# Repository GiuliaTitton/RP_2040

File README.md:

# Descrizione del File main.c

**Nome del File**: main.c
**Progetto**: PSE_2021_2022_SERVER_NTP_LAN
**Cartella**: /FW/TEST_RTC_GPS

## Descrizione
Il programma `main.c` acquisisce l'orario da un modulo GPS e dal RTC (Real-Time Clock) e ne confronta i valori. Se i valori sono diversi, reimposta l'orario del RTC con i valori acquisiti dal GPS. Il programma è diviso in varie sezioni:

1. **Setup dei LED GPIO**: Viene configurato il GPIO per fornire un feedback visivo tramite LED.
2. **Setup di interrupt e interfaccia UART GPS**: Vengono configurati gli interrupt e l'interfaccia UART per comunicare con il modulo GPS.
3. **Lampeggio dei LED**: Viene implementato un lampeggio dei LED per scopi di debug.
4. **Setup I2C e orario iniziale RTC**: Si inizializza la comunicazione I2C e si imposta l'orario iniziale del RTC.
5. **Impostazione dell'allarme**: L'allarme non è impostato nella versione attuale.
6. **Loop continuo composto da**:
   - Lampeggio dei LED.
   - Acquisizione dei dati dal modulo GPS.
   - Acquisizione dei dati dal RTC.
   - Confronto dei dati acquisiti dal modulo GPS e dal RTC.
7. **Controllo dei messaggi in ricezione dal modulo GPS**: Viene gestita la ricezione dei messaggi dal modulo GPS.

## Note
L'allarme non è attualmente impostato nel programma, ma può essere utilizzato per il confronto dei dati acquisiti.

## Autori
- PAGANIN ANDREA
- PASQUINI GIUSEPPE
- TRENTI ELIA
- TITTON GIULIA
- AMORTH MATTEO

## Cambiamenti
- F26/05, Versione A.00.01, 26 Maggio 2022, M. A.: Aggiunte descrizioni delle funzioni e intestazione.
- F19/06, Versione A.00.02, 19 Giugno 2023, M. A.: Aggiunto reset LAN per problema di connessione.

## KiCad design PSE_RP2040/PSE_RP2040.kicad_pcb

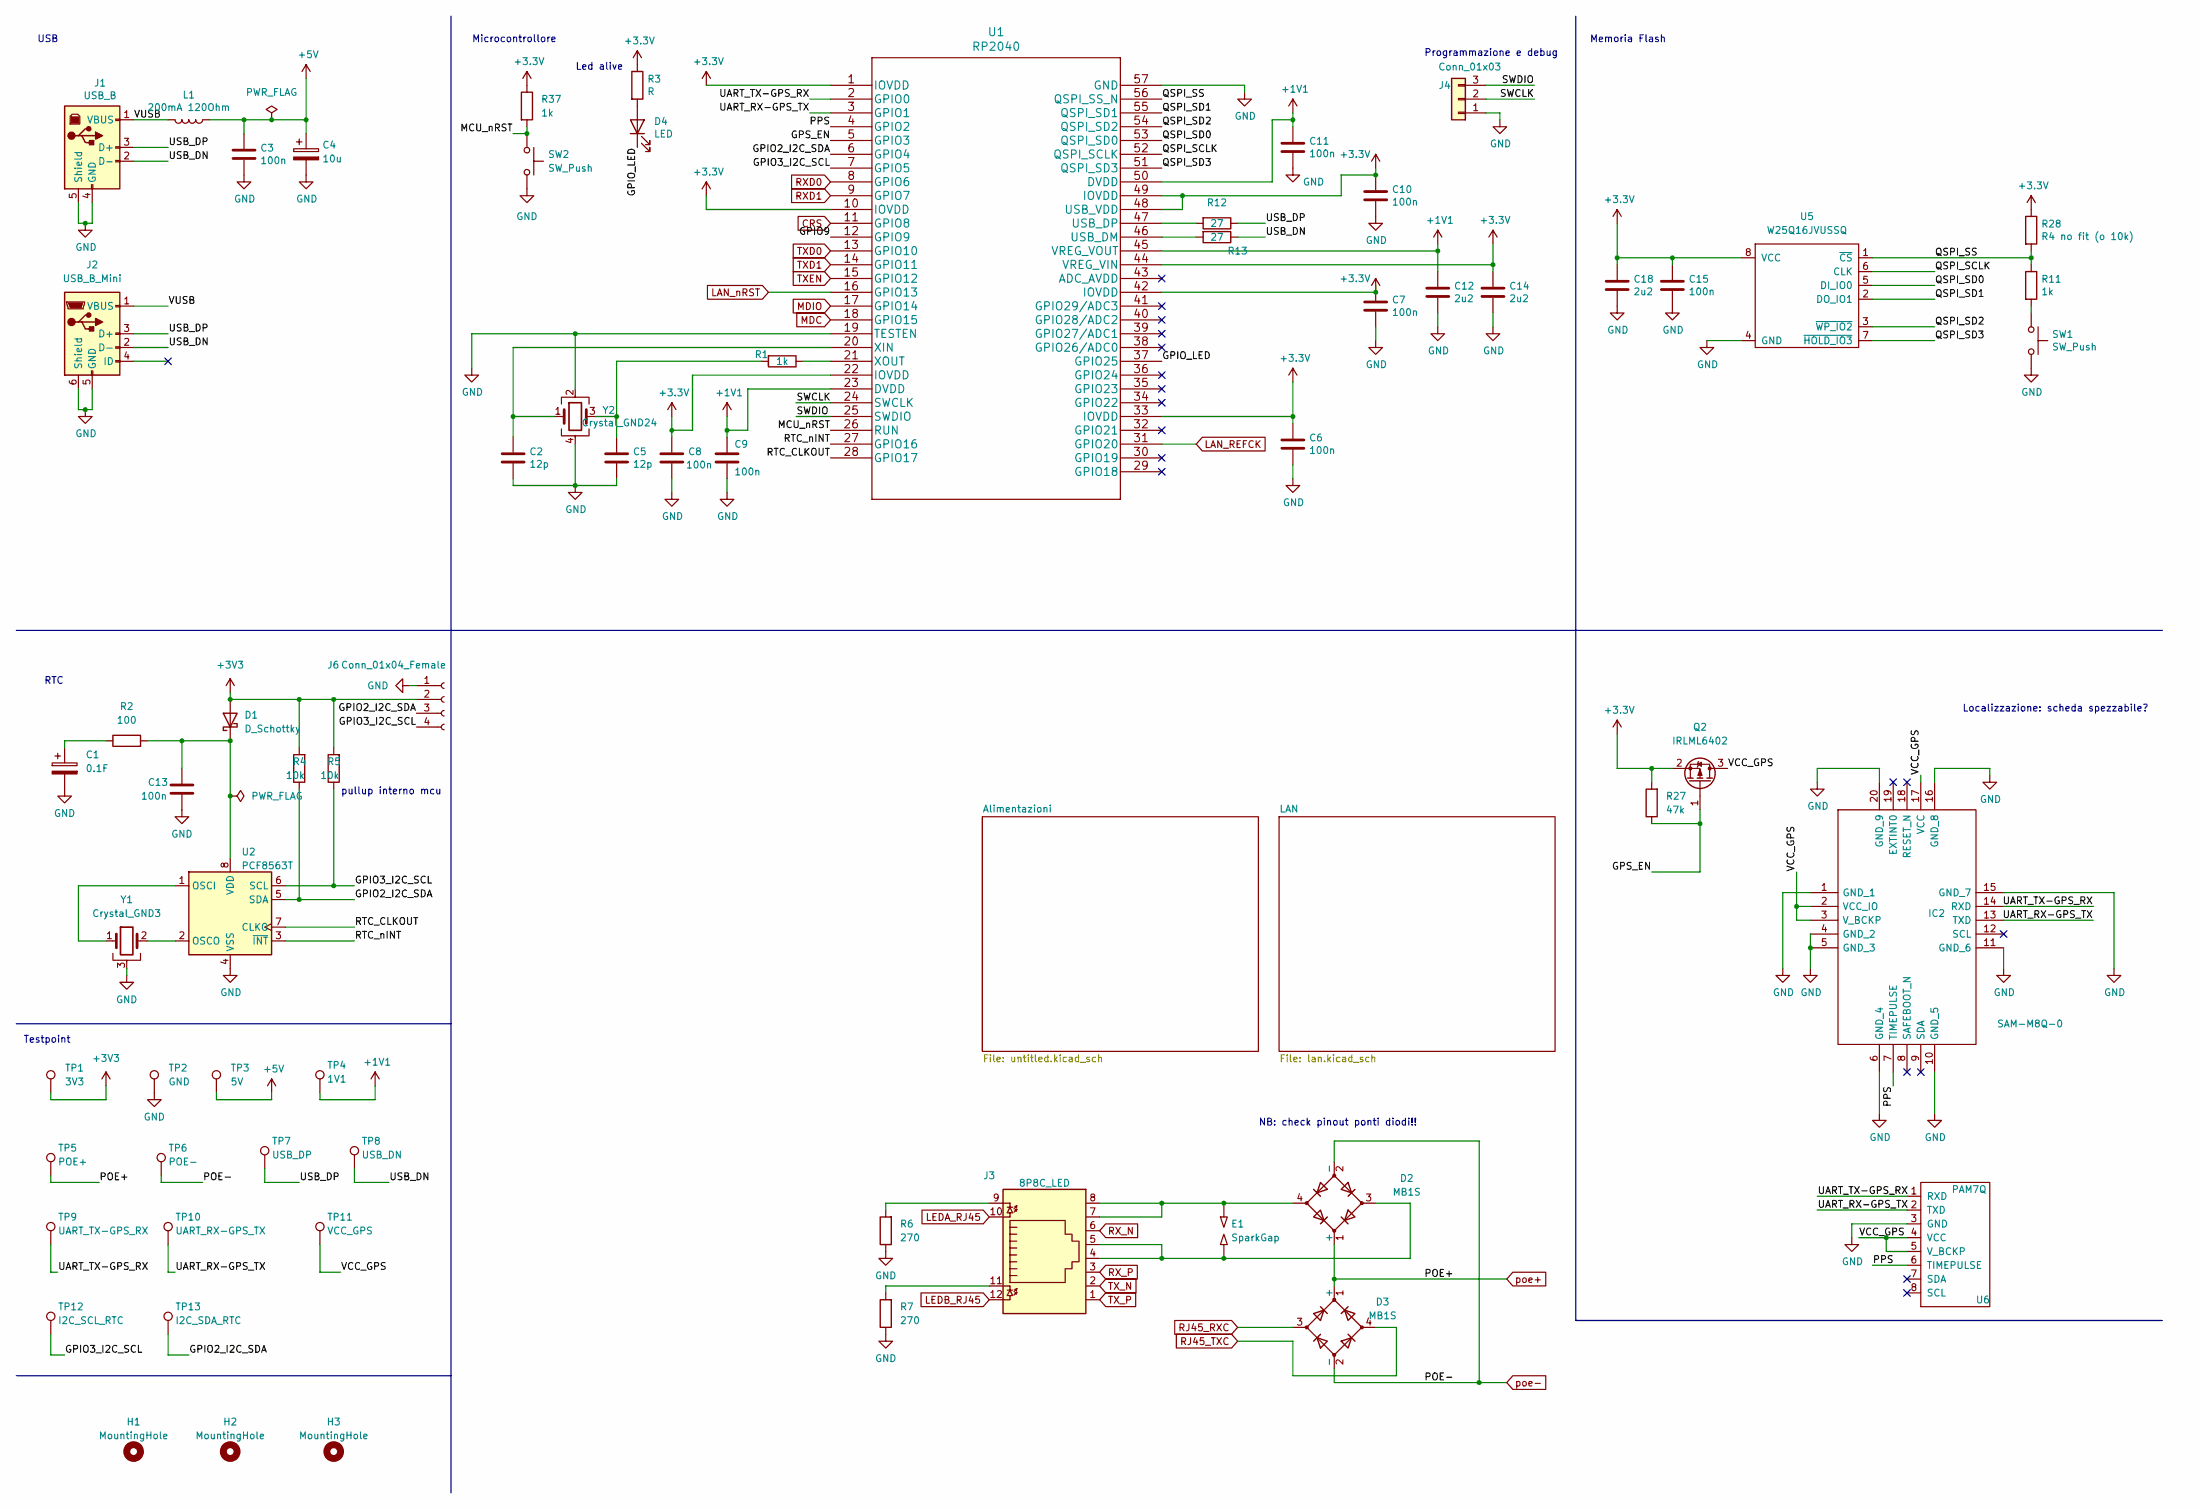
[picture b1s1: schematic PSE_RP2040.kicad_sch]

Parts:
C1: 0.1F; CP_Radial_D10.0mm_P5.00mm
C2, C5: 12p; C_0603_1608Metric
C3, C6, C7, C8, C9, C10, C11, C13, C15: 100n; C_0603_1608Metric
C4: 10u; C_0805_2012Metric
C12, C14, C18: 2u2; C_0603_1608Metric
D1: D_Schottky; D_SMA
D2, D3: MB1S; SO-4_4.4x3.6mm_P2.54mm
D4: LED; LED_0603_1608Metric
E1: SparkGap; SPARK_GAP_TRIANGLE
H1, H2, H3: MountingHole; MountingHole_3mm
IC2: SAM-M8Q-0; SAM-M8Q; Manufacturer_Part_Number SAM-M8Q-0; Mouser Part Number 377-SAM-M8Q-0
J1: USB_B; USB_B_OST_USB-B1HSxx_Horizontal
J2: USB_B_Mini; USB_Mini-B_Wuerth_65100516121_Horizontal
J3: 8P8C_LED; RJ45_Amphenol_RJHSE-5081
J4: Conn_01x03; PinHeader_1x03_P2.54mm_Vertical
J6: Conn_01x04_Female; PinHeader_1x04_P2.54mm_Vertical
L1: 200mA 120Ohm; L_0603_1608Metric
Q2: IRLML6402; SOT-23
R1, R11, R37: 1k; R_0603_1608Metric
R2: 100; R_0603_1608Metric
R3: R; R_0603_1608Metric
R4, R5: 10k; R_0603_1608Metric
R6, R7: 270; R_0603_1608Metric
R12, R13: 27; R_0603_1608Metric
R27: 47k; R_0603_1608Metric
R28: R4 no fit (o 10k); R_0603_1608Metric
SW1, SW2: SW_Push; SW_PUSH_6mm
TP1: 3V3; TestPoint_Loop_D1.80mm_Drill1.0mm_Beaded
TP2: GND; TestPoint_Loop_D1.80mm_Drill1.0mm_Beaded
TP3: 5V; TestPoint_Pad_D1.0mm
TP4: 1V1; TestPoint_Pad_D1.0mm
TP5: POE+; TestPoint_Pad_D1.0mm
TP6: POE-; TestPoint_Pad_D1.0mm
TP7: USB_DP; TestPoint_Pad_D1.0mm
TP8: USB_DN; TestPoint_Pad_D1.0mm
TP9: UART_TX-GPS_RX; TestPoint_Pad_D1.0mm
TP10: UART_RX-GPS_TX; TestPoint_Pad_D1.0mm
TP11: VCC_GPS; TestPoint_Pad_D1.0mm
TP12: I2C_SCL_RTC; TestPoint_Pad_D1.0mm
TP13: I2C_SDA_RTC; TestPoint_Pad_D1.0mm
U1: RP2040; RP2040-QFN-56
U2: PCF8563T; SOIC-8_3.9x4.9mm_P1.27mm
U5: W25Q16JVUSSQ; SOIC-8_5.275x5.275mm_P1.27mm
U6: PAM7Q; PAM-7Q
Y1: Crystal_GND3; Crystal_AT310_D3.0mm_L10.0mm_Horizontal_1EP_style1
Y2: Crystal_GND24; Crystal_SMD_3225-4Pin_3.2x2.5mm

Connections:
+1V1: C9.1, C11.1, C12.1, TP4.1, U1.23 (DVDD), U1.45 (VREG_VOUT), U1.50 (DVDD)
+5V: C3.1, C4.1, L1.1, TP3.1; also elsewhere on the board
/GPIO2_I2C_SDA: J6.3, R4.1, TP13.1, U1.6 (GPIO4), U2.5 (SDA)
/GPIO3_I2C_SCL: J6.4, R5.1, TP12.1, U1.7 (GPIO5), U2.6 (SCL)
/GPIO9: U1.12 (GPIO9)
/GPIO_LED: D4.1 (K), U1.37 (GPIO25)
/GPS_EN: Q2.1 (G), R27.1, U1.5 (GPIO3)
/MCU_nRST: R37.2, SW2.1, U1.26 (RUN)
/PPS: IC2.7 (TIMEPULSE), U1.4 (GPIO2), U6.6 (TIMEPULSE)
/QSPI_SCLK: U1.52 (QSPI_SCLK), U5.6 (CLK)
/QSPI_SD0: U1.53 (QSPI_SD0), U5.5 (DI_IO0)
/QSPI_SD1: U1.55 (QSPI_SD1), U5.2 (DO_IO1)
/QSPI_SD2: U1.54 (QSPI_SD2), U5.3 (~WP_IO2)
/QSPI_SD3: U1.51 (QSPI_SD3), U5.7 (~HOLD_IO3)
/QSPI_SS: R11.1, R28.2, U1.56 (QSPI_SS_N), U5.1 (~CS)
/RTC_CLKOUT: U1.28 (GPIO17), U2.7 (CLKO)
/RTC_nINT: U1.27 (GPIO16), U2.3 (~INT)
/SWCLK: J4.2, U1.24 (SWCLK)
/SWDIO: J4.3, U1.25 (SWDIO)
/UART_RX-GPS_TX: IC2.13 (TXD), TP10.1, U1.3 (GPIO1), U6.2 (TXD)
/UART_TX-GPS_RX: IC2.14 (RXD), TP9.1, U1.2 (GPIO0), U6.1 (RXD)
/USB_DN: J1.2 (D-), J2.2 (D-), R13.1, TP8.1
/USB_DP: J1.3 (D+), J2.3 (D+), R12.1, TP7.1
/VCC_GPS: IC2.2 (VCC_IO), IC2.3 (V_BCKP), IC2.17 (VCC), Q2.3 (D), TP11.1, U6.4 (VCC), U6.5 (V_BCKP)
/VUSB: J1.1 (VBUS), J2.1 (VBUS), L1.2
CRS: U1.11 (GPIO8); also elsewhere on the board
GND: C1.2, C2.2, C3.2, C4.2, C5.2, C6.2, C7.2, C8.2, C9.2, C10.2, C11.2, C12.2, C13.2, C14.2, C15.2, C18.2, IC2.1 (GND_1), IC2.4 (GND_2), IC2.5 (GND_3), IC2.6 (GND_4), IC2.10 (GND_5), IC2.11 (GND_6), IC2.15 (GND_7), IC2.16 (GND_8), IC2.20 (GND_9), J1.4 (GND), J1.5 (Shield), J2.5 (GND), J2.6 (Shield), J4.1, J6.1, R6.1, R7.1, SW1.2, SW2.2, TP2.1, U1.19 (TESTEN), U1.57 (GND), U2.4 (VSS), U5.4 (GND), U6.3 (GND), Y1.3, Y2.2, Y2.4; also elsewhere on the board
LAN_REFCK: U1.31 (GPIO20); also elsewhere on the board
LAN_nRST: U1.16 (GPIO13); also elsewhere on the board
LEDA_RJ45: J3.10; also elsewhere on the board
LEDB_RJ45: J3.12; also elsewhere on the board
MDC: U1.18 (GPIO15); also elsewhere on the board
MDIO: U1.17 (GPIO14); also elsewhere on the board
unnamed: C1.1, R2.1
unnamed: C2.1, U1.20 (XIN), Y2.1
unnamed: C5.1, R1.2, Y2.3
unnamed: D2.3, E1.1, J3.4, J3.5
unnamed: D2.4, E1.2, J3.7, J3.8
unnamed: D4.2 (A), R3.2
unnamed: J3.9, R6.2
unnamed: J3.11, R7.2
unnamed: R1.1, U1.21 (XOUT)
unnamed: R11.2, SW1.1
unnamed: R12.2, U1.47 (USB_DP)
unnamed: R13.2, U1.46 (USB_DM)
unnamed: U2.1 (OSCI), Y1.1
unnamed: U2.2 (OSCO), Y1.2
RJ45_RXC: D3.3; also elsewhere on the board
RJ45_TXC: D3.4; also elsewhere on the board
RXD0: U1.8 (GPIO6); also elsewhere on the board
RXD1: U1.9 (GPIO7); also elsewhere on the board
RX_N: J3.6; also elsewhere on the board
RX_P: J3.3; also elsewhere on the board
TXD0: U1.13 (GPIO10); also elsewhere on the board
TXD1: U1.14 (GPIO11); also elsewhere on the board
TXEN: U1.15 (GPIO12); also elsewhere on the board
TX_N: J3.2; also elsewhere on the board
TX_P: J3.1; also elsewhere on the board
poe+: D2.1 (+), D3.1 (+), TP5.1; also elsewhere on the board
poe-: D2.2 (-), D3.2 (-), TP6.1; also elsewhere on the board

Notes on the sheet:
Memoria Flash
USB
pullup interno mcu
RTC
Led alive
Programmazione e debug
Testpoint
NB: check pinout ponti diodi!!
Localizzazione: scheda spezzabile?
Microcontrollore

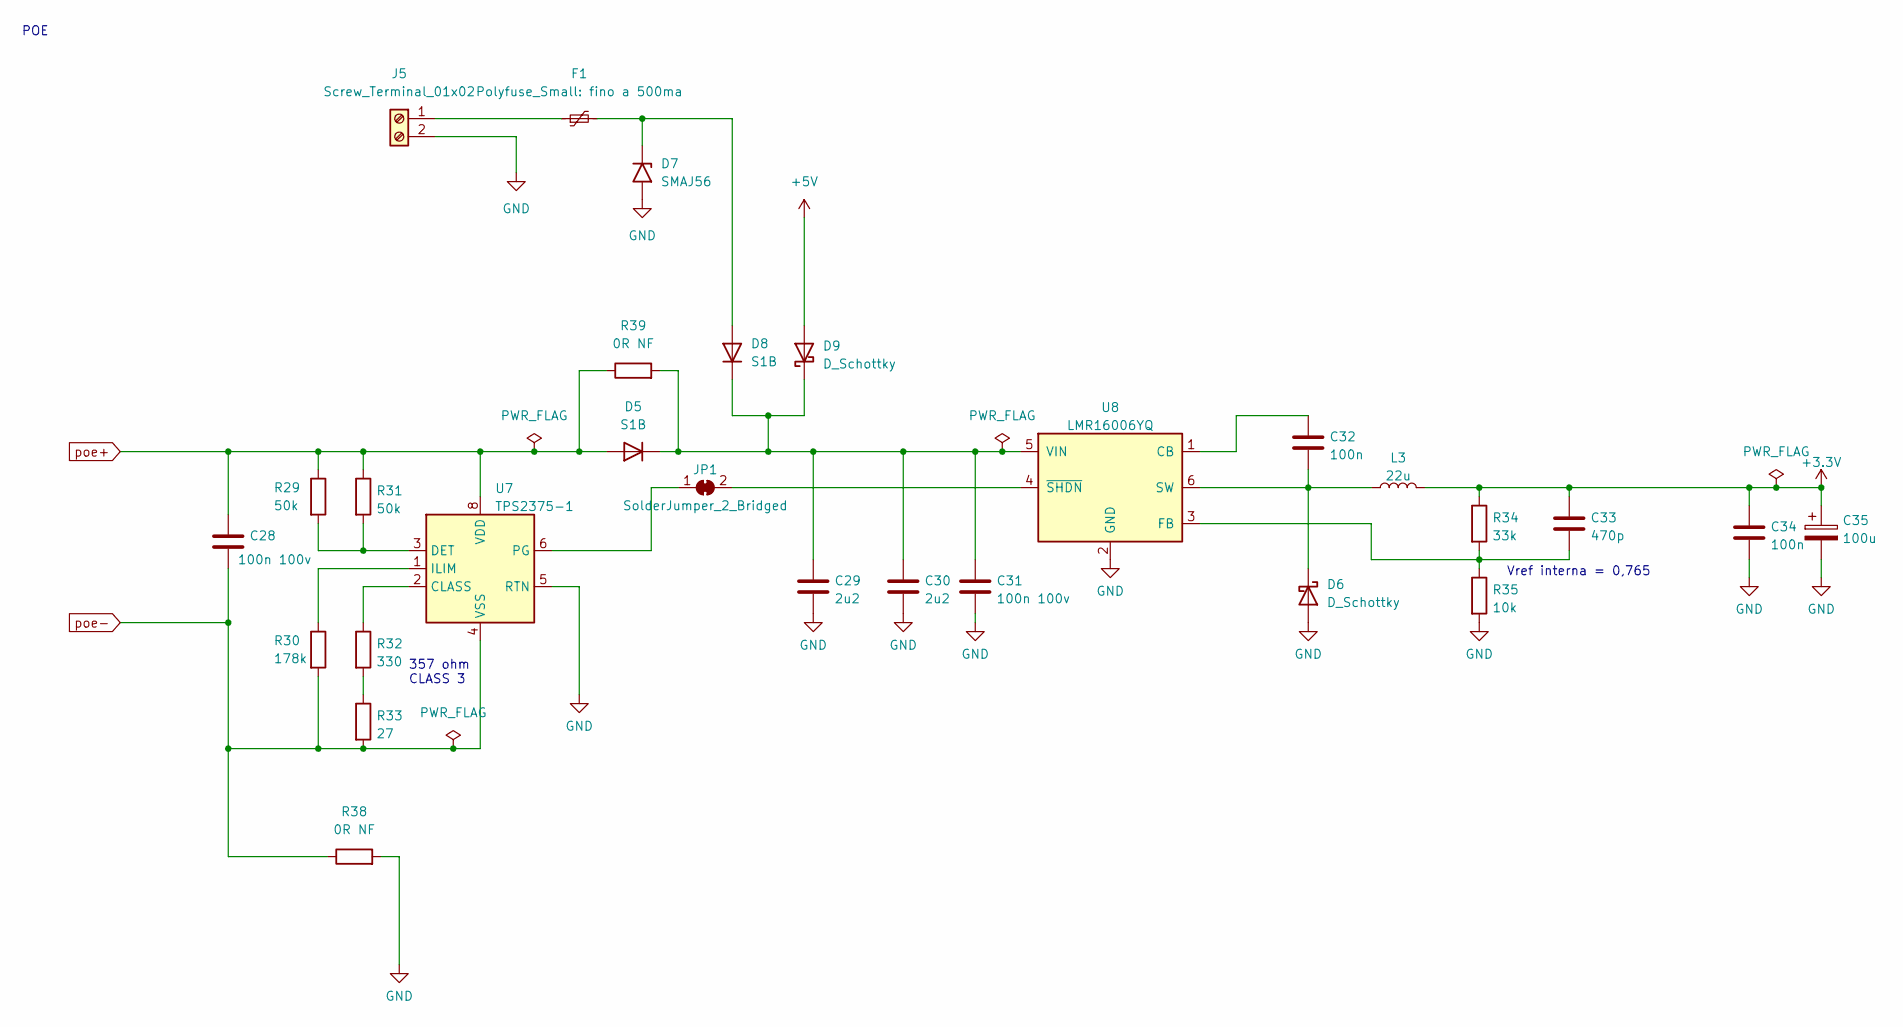
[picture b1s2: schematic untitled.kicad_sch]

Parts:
C28, C31: 100n 100v; C_0603_1608Metric
C29, C30: 2u2; C_0603_1608Metric
C32, C34: 100n; C_0603_1608Metric
C33: 470p; C_0603_1608Metric
C35: 100u; C_0805_2012Metric
D5, D8: S1B; D_SMA
D6, D9: D_Schottky; D_SMA
D7: SMAJ56; D_SMA
F1: Polyfuse_Small: fino a 500ma; Fuse_1812_4532Metric
J5: Screw_Terminal_01x02; TerminalBlock_Phoenix_MKDS-1,5-2-5.08_1x02_P5.08mm_Horizont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
JP1: SolderJumper_2_Bridged; SolderJumper-2_P1.3mm_Bridged_Pad1.0x1.5mm
L3: 22u; L_Vishay_IFSC-1515AH_4x4x1.8mm
R29, R31: 50k; R_0603_1608Metric
R30: 178k; R_0603_1608Metric
R32: 330; R_0603_1608Metric
R33: 27; R_0603_1608Metric
R34: 33k; R_0603_1608Metric
R35: 10k; R_0603_1608Metric
R38, R39: 0R NF; R_0603_1608Metric
U7: TPS2375-1; SOIC-8_5.275x5.275mm_P1.27mm
U8: LMR16006YQ; SOT-23-6

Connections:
+5V: D9.2 (A); also elsewhere on the board
GND: C29.2, C30.2, C31.2, C34.2, C35.2, D6.2 (A), D7.2 (A2), J5.2, R35.2, R38.2, U7.5 (RTN), U8.2 (GND); also elsewhere on the board
unnamed: C29.1, C30.1, C31.1, D5.1 (K), D8.1 (K), D9.1 (K), R39.2, U8.5 (VIN)
unnamed: C32.1, U8.1 (CB)
unnamed: C32.2, D6.1 (K), L3.1, U8.6 (SW)
unnamed: C33.2, R34.2, R35.1, U8.3 (FB)
unnamed: D7.1 (A1), D8.2 (A), F1.2
unnamed: F1.1, J5.1
unnamed: JP1.1 (A), U7.6 (PG)
unnamed: JP1.2 (B), U8.4 (~SHDN)
unnamed: R29.2, R31.2, U7.3 (DET)
unnamed: R30.1, U7.1 (ILIM)
unnamed: R32.1, U7.2 (CLASS)
unnamed: R32.2, R33.1
poe+: C28.1, D5.2 (A), R29.1, R31.1, R39.1, U7.8 (VDD); also elsewhere on the board
poe-: C28.2, R30.2, R33.2, R38.1, U7.4 (VSS); also elsewhere on the board

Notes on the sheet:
Vref interna = 0,765
POE
357 ohm CLASS 3

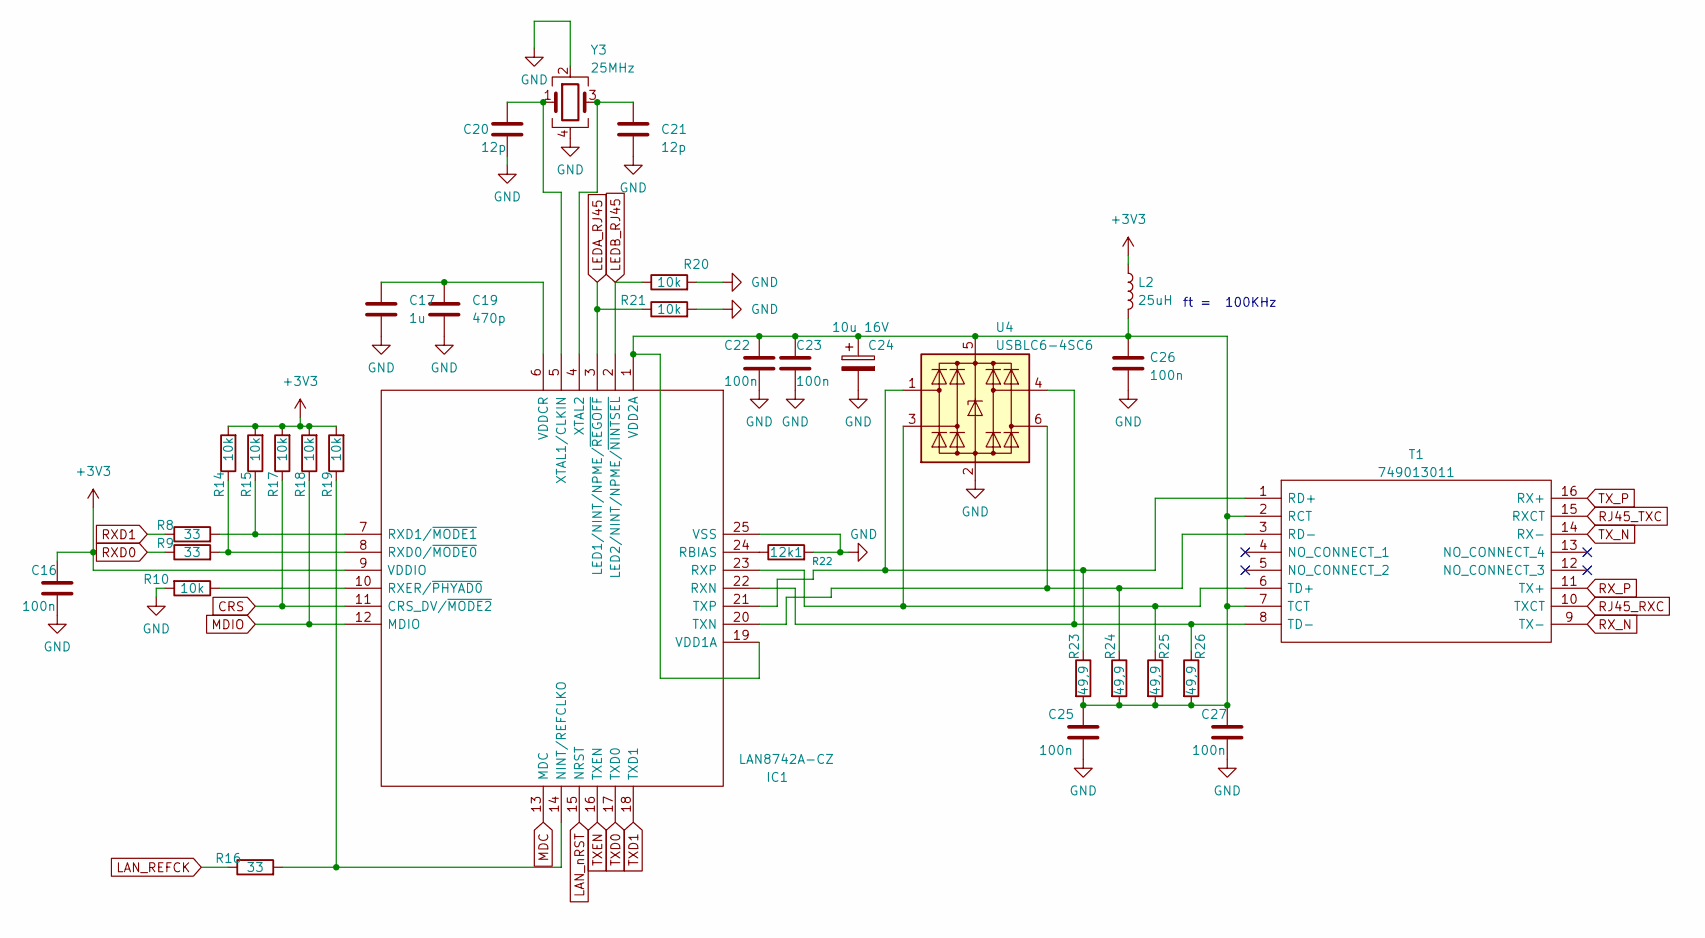
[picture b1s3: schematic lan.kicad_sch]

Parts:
C16, C22, C23, C25, C26, C27: 100n; C_0603_1608Metric
C17: 1u; C_0603_1608Metric
C19: 470p; C_0603_1608Metric
C20, C21: 12p; C_0603_1608Metric
C24: 10u 16V; C_0805_2012Metric
IC1: LAN8742A-CZ; HVQFN-24-1EP_4x4mm_P0.5mm_EP2.5x2.5mm_ThermalVias; Mouser Part Number 579-LAN8742A-CZ
L2: 25uH; L_0603_1608Metric
R8, R9, R16: 33; R_0603_1608Metric
R10, R14, R15, R17, R18, R19, R20, R21: 10k; R_0603_1608Metric
R22: 12k1; R_0603_1608Metric
R23, R24, R25, R26: 49,9; R_0603_1608Metric
T1: 749013011; Transformer_Ethernet_Wuerth_749013011A; Mouser Part Number 710-749013011
U4: USBLC6-4SC6; SOT-23-6
Y3: 25MHz; Crystal_SMD_3225-4Pin_3.2x2.5mm

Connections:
CRS: IC1.11 (CRS_DV/~MODE2), R17.1; also elsewhere on the board
GND: C16.2, C17.2, C19.2, C20.2, C21.2, C22.2, C23.2, C24.2, C25.2, C26.2, C27.2, IC1.25 (VSS), R10.2, R20.2, R21.2, R22.2, U4.2 (GND), Y3.2, Y3.4; also elsewhere on the board
LAN_REFCK: R16.1; also elsewhere on the board
LAN_nRST: IC1.15 (NRST); also elsewhere on the board
LEDA_RJ45: IC1.3 (LED1/NINT/NPME/~REGOFF), R21.1; also elsewhere on the board
LEDB_RJ45: IC1.2 (LED2/NINT/NPME/~NINTSEL), R20.1; also elsewhere on the board
MDC: IC1.13 (MDC); also elsewhere on the board
MDIO: IC1.12 (MDIO), R18.1; also elsewhere on the board
unnamed: C17.1, C19.1, IC1.6 (VDDCR)
unnamed: C20.1, IC1.5 (XTAL1/CLKIN), Y3.1
unnamed: C21.1, IC1.4 (XTAL2), Y3.3
unnamed: C22.1, C23.1, C24.1, C25.1, C26.1, C27.1, IC1.1 (VDD2A), IC1.19 (VDD1A), L2.2, R23.2, R24.2, R25.2, R26.2, T1.2 (RCT), T1.7 (TCT), U4.5 (VBUS)
unnamed: IC1.7 (RXD1/~MODE1), R8.2, R15.1
unnamed: IC1.8 (RXD0/~MODE0), R9.2, R14.1
unnamed: IC1.10 (RXER/~PHYAD0), R10.1
unnamed: IC1.14 (NINT/REFCLKO), R16.2, R19.1
unnamed: IC1.20 (TXN), R24.1, T1.3 (RD-), U4.6 (I/O4)
unnamed: IC1.21 (TXP), R23.1, T1.1 (RD+), U4.1 (I/O1)
unnamed: IC1.22 (RXN), R26.1, T1.8 (TD-), U4.4 (I/O3)
unnamed: IC1.23 (RXP), R25.1, T1.6 (TD+), U4.3 (I/O2)
unnamed: IC1.24 (RBIAS), R22.1
RJ45_RXC: T1.10 (TXCT); also elsewhere on the board
RJ45_TXC: T1.15 (RXCT); also elsewhere on the board
RXD0: R9.1; also elsewhere on the board
RXD1: R8.1; also elsewhere on the board
RX_N: T1.9 (TX-); also elsewhere on the board
RX_P: T1.11 (TX+); also elsewhere on the board
TXD0: IC1.17 (TXD0); also elsewhere on the board
TXD1: IC1.18 (TXD1); also elsewhere on the board
TXEN: IC1.16 (TXEN); also elsewhere on the board
TX_N: T1.14 (RX-); also elsewhere on the board
TX_P: T1.16 (RX+); also elsewhere on the board

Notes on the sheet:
ft = 100KHz

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
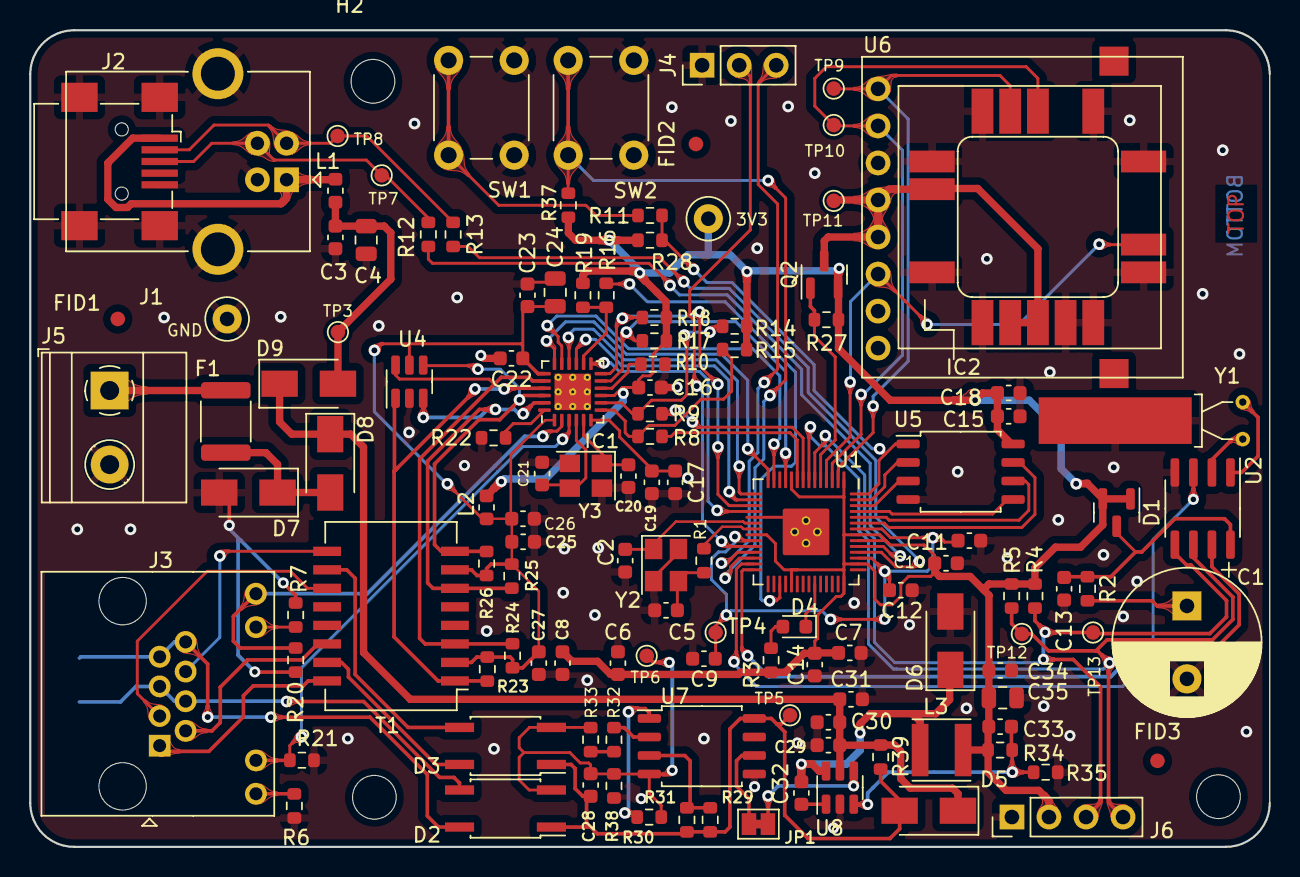
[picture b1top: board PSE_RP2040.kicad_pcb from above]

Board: 2 copper layers, 85.0 x 56.0 mm, 129 parts (1 on the bottom side), 86 nets.

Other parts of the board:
FID1, FID2, FID3: Fiducial_1mm_Mask2mm

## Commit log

2022-03-13 Aggiunta USB
2022-03-13 Create README.md
    commit di prova
2022-03-13 extracted files
2022-03-13 changed dir
2022-03-13 written prova4
2022-03-13 Revert "written prova4"
    This reverts commit d653c9951a9aa16452c87e5e3175ff5a990ef213.
2022-03-14 scritto prova matteo
2022-03-14 Update README.md
    bla bla
2022-03-15 Modifica schema kicad
    Aggiunti librerie, datasheet e componenti
2022-03-17 Modifica quarzo
2022-03-19 Aggiornamento schematico
    Passaggio a Kicad6, aggiunti elementi interfaccia LAN (iniziato)
2022-03-19 sostituzione componenti
2022-03-19 pt.2
2022-03-20 ds lan
2022-03-20 finito circuito lan
2022-03-20 USBLC6-4SC6 ds
2022-03-20 aggiunto pdf schematico(provvisorio)
2022-03-21 added fw folder
2022-03-21 added STRUTTURA_BASE to FW
2022-03-21 added bin
2022-03-21 trattino
2022-03-21 added pico-sdk
2022-03-21 test sdk
    Funziona. Aggiunto commento in cmake
2022-03-21 schematico completato
2022-03-21 PCF8563 Real time clock scheda dati
2022-03-21 rtc aggiunta
2022-03-21 Presentazione
2022-03-21 aggiunto datasheet pmos
2022-03-22 modifiche schematico
    cancellata sezione alimentazione non più necessaria (usiamo switching del poe)
2022-03-23 schematico
2022-03-23 backup file
2022-03-23 datasheet
2022-03-24 schematico rtc
2022-03-24 documentazione diodo
2022-03-24 aggiornamento schematico
2022-03-24 modifica cmakelists
    aggiunte impostazioni per il pull del pico-sdk
2022-03-24 annotato schematico + pwr flag
2022-03-25 aggiornato cmakelists.txt del fw
2022-03-26 modifica pull sdk
    tolto direttiva con percorso assoluto dell'sdk. avere sempre la cartella sdk parallela a quella di progetto.
2022-03-26 MountingHole+estetica
2022-03-28 footprint sam
2022-03-28 aggiunta libreria rp2040
2022-03-28 schematico
    Cambio trasformatore
    aggiunto foglio
2022-03-28 memoria
2022-03-28 Creata impronta base pam 7q (GPS2))
2022-03-29 aggiornamento schematico
    etichette globali, testpoint, assegnamento footprint (ne mancano ancora)
2022-03-29 assegnamento footprint PAM7Q
2022-03-29 footprint flash
2022-03-29 area pcb
2022-03-30 aggiunto Footprint sam-m8q e aggiornato pam-7q
    è una bozza, una volta controllate le misure si possono togliere le linee che ho messo per avere i riferimenti
2022-03-30 footprint usb micro e crystal
2022-03-30 footprint, aggiunto bottone rst
2022-03-30 OR a diodi, connettore ext PoE
2022-03-31 aggiunto pico-rmii-eth in FW
2022-03-31 tolta cartella build da FW/rmii
2022-03-31 valore resistenze lan
2022-03-31 correzioni schema
2022-03-31 update footprint
2022-04-01 Link super condensatore e connettore RJ45
2022-04-04 footprint, assegnamento
    etichette (label)
2022-04-04 modifiche lezione
    usb mini,
    check s1b
2022-04-05 footprint
    cambiato footprint rp2040 (ora c'è quello con le vias) e footprint tps2375
2022-04-05 allungate pad footprint micro
2022-04-06 check pin, footprint e symb mem
    tolto pin 9 al simbolo memoria
2022-04-06 piazzamento componenti pcb 1
    piazzamento di massima
2022-04-06 piazzamento componenti pcb
2022-04-06 contorni raspberry pi 4
    mantenersi entro i 56 mm di larghezza. in lunghezza si può andare oltre gli 85 mm
2022-04-07 pad micro, footprint, posizionamento componenti pcb
2022-04-07 pcb
    spostati componenti
2022-04-07 pcb merdaccia
2022-04-07 pcb parz. Aggiornato
2022-04-07 PCB
    Sbroglio parte alimentazione
2022-04-08 PCB
    Aggiunto strato rame bottom, tolto mounting hole 4 dallo schematico, aggiunti fiducial (solo sul PCB), riduzione margine scheda, sbroglio.
    (larghezza max piste in uscita dal micro 7 mils)
2022-04-08 modifiche schematico e pcb
    Invertito tx e rx tra trasformatore e modulo lan per sbroglio più comodo.
    Fatto posto per allontanare gps dal bordo e collegate varie cose
2022-04-08 PCB_LAN
    corretto alimentazione gps (VDDIO)
2022-04-08 sbroglio micro
2022-04-09 sbroglio pcb
2022-04-09 footprint sam8
2022-04-09 sbroglio pcb, aggiunte vias
2022-04-09 scritte top, bottom su rame, serigrafia TP
2022-04-09 Leggi descrizione per verifica
    -tolte aree rame sotto pin non usati.
    -spostate le serigrafie
    -portato a 11 gli errori, da verificare se
    VDD1A e VDD2A di IC1 devono essere connessi? ->Errori ridotti a 11
2022-04-11 footprint micro con piazzole paste, gerber
2022-04-11 ottimizzazioni
2022-04-11 impronta pam7 (pad saldatura)
    TODO: rigenerare gerber
2022-04-12 Gerber controllati
2022-04-12 aggiunto gerber top paste per lamina
2022-04-20 aggiunta bom pdf
2022-04-20 progetto test rtc e gps in FW
2022-04-23 file comunicazione gps
2022-04-23 bom
    aggiunto file comunicazione gps
2022-04-23 inseriti valori mancanti
2022-04-26 FW/ test rtc, get data
2022-04-27 routine uart, callback gpio irq
2022-05-03 Modifiche RTC - descrizione
    Modificato indirizzo rtc e registro da puntare. Controllare se effettivamente sono corrette le modifiche con il datasheet (ci sono segnate le pagine nei file pcf8563.c e pcf8563.h)
2022-05-04 modifica driver rtc,
    aggiunta scrittura registro secondi. TODO: scrivere gli altri dati
2022-05-04 funzioni rtc
2022-05-05 fw/rtc functions
2022-05-05 fw/ rtc2
2022-05-07 FW/ irq GPS + GPGGA
2022-05-07 messaggi gps tempo e dat
    manca ancora l'estrazione in numeri delle stringhe
2022-05-08 aggiunte funzionalità main
    aggiunta conversione in numeri dei caratteri da gps
2022-05-08 spostate variabili da globali a locali
2022-05-08 modifiche rtc
    aggiunta funzione per impostare timer su MCP7940.c e .h
2022-05-12 blink led in rmii-pico
2022-05-15 BLINK_DBG RMII
2022-05-16 link funziona
    grazie salvalu
2022-05-17 nulla, solo per fare un commit :D
2022-05-18 Aggiunta documentazione
    Documentazione e commenti
2022-05-19 varie cose
    invio messaggio prova http
    corretta conversione ascii numeri
2022-05-19 rtc test
2022-05-20 correzioni gps
2022-05-23 modifiche httpd
    debug in printf
2022-05-23 modifica file html
    ricompilato e sistemato fsdata.c
    ora la richiesta GET HTTP ottiene "000000"
2022-05-23 modifiche httpd riga 2270
    Aggiunta stampa in debug di alcuni caratteri di index.html
    Da implementare la modifica dei campi stessi
2022-05-24 httpd.c mod
2022-05-25 rimossi const da fsdata.c
2022-05-25 mcp FW
2022-05-26 integrazione rtc gps
2022-05-26 rtc +gps controllo tempo
2022-05-26 aggiunte descrizioni file
2022-05-29 aggiunto progetto merge
    sistemare inclusione i2c
2022-05-30 relazione+merge ethernet-rtc-gps
2022-05-30 bug rtc corretto
2023-06-19 reset lan + apertura rapida con file
    Aggiunto reset lan per la connessione che elimina il bug del staccare e riagganciare il cavo ethernet. In più il file .code-workspace apre direttamente la cartella del progetto in vscode senza dover 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
2023-10-05 mi annoiavo
2023-10-05 mi annoio
2023-11-03 added support for samm8q gps
